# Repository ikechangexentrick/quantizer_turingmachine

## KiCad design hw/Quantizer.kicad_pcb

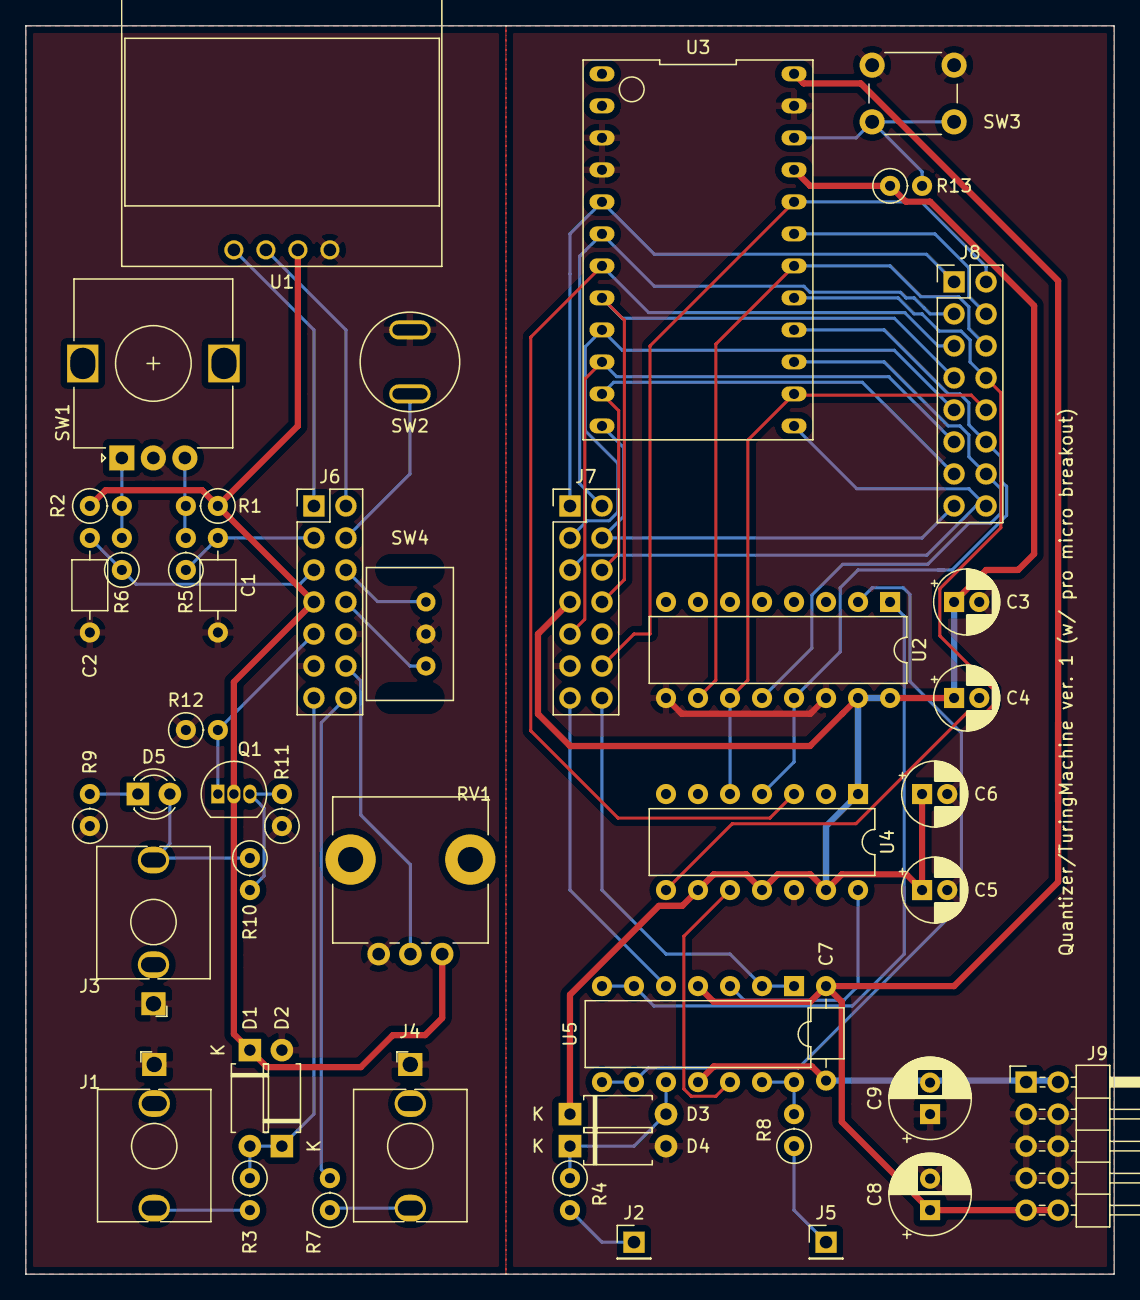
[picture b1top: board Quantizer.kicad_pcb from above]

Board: 2 copper layers, 86.4 x 99.1 mm, 47 parts (0 on the bottom side), 49 nets.

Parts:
C1, C2, C7: 0.1u; C_Axial_L3.8mm_D2.6mm_P7.50mm_Horizontal
C3, C5: 10u; CP_Radial_D5.0mm_P2.00mm
C4, C6: 1u; CP_Radial_D5.0mm_P2.00mm
C8, C9: 100u; CP_Radial_D6.3mm_P2.50mm
D1, D2, D3, D4: D; D_A-405_P7.62mm_Horizontal
D5: LED; LED_D3.0mm
J1: Audio_in; mono_jack_3.5mm
J2: Audio_in_2; PinHeader_1x01_P2.54mm_Vertical
J3: gate_in; mono_jack_3.5mm
J4: Audio_out; mono_jack_3.5mm
J5: Audio_out_2; PinHeader_1x01_P2.54mm_Vertical
J6, J7: Conn_02x07_Odd_Even; PinHeader_2x07_P2.54mm_Vertical
J8: breakout; PinHeader_2x08_P2.54mm_Vertical
J9: power_bus; PinHeader_2x05_P2.54mm_Horizontal
Q1: 2SC1815; TO-92_Inline
R1, R2, R5, R6, R9, R13: 10k; R_Axial_DIN0207_L6.3mm_D2.5mm_P2.54mm_Vertical
R3, R4, R10, R11, R12: 100k; R_Axial_DIN0207_L6.3mm_D2.5mm_P2.54mm_Vertical
R7, R8: 1k; R_Axial_DIN0207_L6.3mm_D2.5mm_P2.54mm_Vertical
RV1: param; Potentiometer_Alps_RK09L_Single_Vertical
SW1: command; RotaryEncoder_Alps_EC12E_Vertical_H20mm
SW2: btn_enter; push_button
SW3: reset; SW_PUSH_6mm
SW4: write; SW_DPDT_Momentary
U1: OLED_Display_SSD1306; aki_OLED_0.96in
U2: MCP3208; DIP-16_W7.62mm
U3: ProMicro; Pro_Micro_Top_side_Up
U4: MCP4922; DIP-14_W7.62mm
U5: TL074; DIP-14_W7.62mm

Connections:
+5V: C3.1, C4.1, C5.1, C6.1, D1.1, D3.1, J6.7, J7.7, Q1.2, R1.1, R2.1, R13.1, RV1.3, U1.2, U2.15, U2.16, U3.21, U4.1, U4.9, U4.11, U4.13
+12V: C7.1, C8.1, J9.9, J9.10, U3.24, U5.4
-12V: C7.2, C9.2, J9.1, J9.2, U5.11
/Sheet628BAE91/TM_off: J6.6, SW4.1
/Sheet628BAE91/TM_on: J6.8, SW4.3
/Sheet628BAE91/TM_pot: J6.12, RV1.2
/Sheet628BAE91/audio_in_1: D1.2, D2.1, J6.13, R3.1
/Sheet628BAE91/audio_out_1: J6.14, R7.2
/Sheet628BAE91/btn_enter: J6.4, SW2.2
/Sheet628BAE91/gate: J6.9, Q1.1, R12.2
/Sheet628BAE91/i2c_clk: J6.2, U1.3
/Sheet628BAE91/i2c_data: J6.1, U1.4
/Sheet628BAE91/re_1: C2.1, J6.5, R6.1
/Sheet628BAE91/re_2: C1.1, J6.3, R5.1
/Sheet628BB73E/CS_AD: J8.6, U2.10, U3.18
/Sheet628BB73E/CS_DA: J8.5, U3.7, U4.3
/Sheet628BB73E/D14: J8.14, U2.12, U3.15
/Sheet628BB73E/D15: J8.12, U2.13, U3.16, U4.4
/Sheet628BB73E/D16: J8.10, U2.11, U3.14, U4.5
/Sheet628BB73E/D18_A0: J8.8, U3.17, U4.8
/Sheet628BB73E/D20_A2: J8.4, U3.19
/Sheet628BB73E/TM_off: J7.6, J8.13, U3.11
/Sheet628BB73E/TM_on: J7.8, J8.7, U3.8
/Sheet628BB73E/TM_pot: J7.12, J8.2, U3.20
/Sheet628BB73E/audio_in_1: J7.13, U5.5
/Sheet628BB73E/audio_out_1: J7.14, U5.1, U5.2
/Sheet628BB73E/btn_enter: J7.4, J8.15, U3.12
/Sheet628BB73E/gate: J7.9, J8.11, U3.10
/Sheet628BB73E/i2c_clk: J7.2, J8.3, U3.6
/Sheet628BB73E/i2c_data: J7.1, J8.1, U3.5
/Sheet628BB73E/re_1: J7.5, J8.16, U3.13
/Sheet628BB73E/re_2: J7.3, J8.9, U3.9
GND: C1.2, C2.2, C3.2, C4.2, C5.2, C6.2, C8.2, C9.1, D2.2, D4.2, J1.S, J3.S, J4.S, J6.10, J6.11, J7.10, J7.11, J9.3, J9.4, J9.5, J9.6, J9.7, J9.8, R9.1, R11.1, R12.1, RV1.1, SW1.C, SW2.1, SW3.2, SW4.2, U1.1, U2.9, U2.14, U3.3, U3.4, U3.23, U4.12
unnamed: D3.2, D4.1, R4.1, U5.10
unnamed: D5.1, R9.2
unnamed: D5.2, J3.T, R10.1
unnamed: J1.T, R3.2
unnamed: J2.1, R4.2
unnamed: J4.T, R7.1
unnamed: J5.1, R8.1
unnamed: Q1.3, R10.2, R11.2
unnamed: R1.2, R5.2, SW1.B
unnamed: R2.2, R6.2, SW1.A
unnamed: R8.2, U5.13, U5.14
unnamed: R13.2, SW3.1, U3.22
unnamed: U2.1, U5.6, U5.7
unnamed: U2.2, U5.8, U5.9
unnamed: U4.10, U5.12
unnamed: U4.14, U5.3

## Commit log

2022-06-20 Quantizer, first version. Works, but no user interface.
2022-06-20 Turing Machine clone.
2022-06-20 Followed library's update.
2022-06-20 Modified to be able to control the sequence length. Refactored codes; separated into library/{AD_DA_Converters,Display_OLED}.
2022-06-20 Software: followed library's update. Hardware: appended kicad project files.
2022-06-20 Added an user interface. Input via a rotary encoder and a button, and output via the serial terminal.
2022-06-20 Introduced Display class, to collect procedures for showing menu.
    Adjusted pin assigns.
2022-06-20 Modified to use AD_DA_Converters and Display libraries. Separated codes for user interface into quantizer_ui.cpp.
2022-07-04 Turing Machine: added Gate mode.
